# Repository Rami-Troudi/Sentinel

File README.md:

# Sentinel

Plateforme de prévention routière basée sur un boîtier embarqué, de l’analyse IA et un système de récompenses pour la conduite responsable.  
Projet développé dans le cadre du hackathon **Hack For Good 4.0 – Forum INSAT Entreprise**, en partenariat avec **Lloyd Assurance**.

---

## 1. Introduction

**Sentinel** est une solution de télématique intelligente qui combine :

- un **boîtier embarqué ESP32** installé dans le véhicule ;
- une **application mobile** pour le conducteur ;
- une **infrastructure cloud** et une **API backend** ;
- un **module d’intelligence artificielle** pour analyser la conduite ;
- un **dashboard web** pour l’assureur.

L’objectif est double :

1. **Mieux comprendre et anticiper le risque** (conducteurs et zones).  
2. **Encourager et récompenser la conduite responsable** via un système d’éco-points échangeables contre des avantages.

---

## 2. Problématique

Les assureurs automobiles, font face à plusieurs limitations :

- Évaluation du risque principalement **a posteriori**, après sinistre.
- Données comportementales **peu spécifiques** et difficilement exploitables.
- Solutions basées sur smartphone **peu fiables** (capteurs limités, usage intermittent, contournement possible).
- **Absence d’incitation positive** claire pour encourager la bonne conduite.
- Manque de **cartographie dynamique** des zones routières à risque.
- Nécessité de s’inscrire dans une démarche **RSE** crédible (sécurité, éco-conduite, inclusion).

Conséquences :

- sinistralité plus élevée que nécessaire ;
- difficulté à adapter les primes au comportement réel ;
- faible engagement des assurés ;
- opportunités perdues en matière de prévention et de fidélisation.

---

## 3. Description de la solution

### 3.1 Vue d’ensemble

Sentinel propose un écosystème complet qui relie :

- les **données terrain** (capteurs dans le véhicule) ;
- une **analyse IA** à plusieurs niveaux (événements, comportements, zones) ;
- un **système de scoring** et de **classification des risques** ;
- un **programme d’éco-points** qui transforme la prévention en valeur pour le client ;
- un **outil de pilotage** pour l’assureur.

### 3.2 Fonctionnalités principales

- Collecte de télémétrie : accélérations, freinages brusques, virages, vibrations, etc.
- Détection d’événements de conduite à risque.
- Calcul d’un **score de conduite dynamique** pour chaque conducteur.
- Classification des **zones géographiques à risque**.
- Génération d’**éco-points** pour les conducteurs responsables.
- Échange des éco-points contre :
  - réductions sur la prime d’assurance,
  - bons et avantages chez les partenaires de l’assureur.
- Dashboard pour Lloyd :
  - vision agrégée des risques,
  - cartographie des zones,
  - suivi des indicateurs RSE et du programme de récompenses.
  - Classification des conduteurs selon le risque

---

## 4. Schématisation de la communication dans le système

Schéma logique des flux de données et des interactions :

```text

           │
           ▼
   [Boîtier embarqué ESP32]
  - Capteurs (accéléromètre, gyroscope,
  vibration, etc.)
  - Prétraitement local (seuils)
           │
    Wi-Fi / Bluetooth 
           │
           ▼
      [Application Mobile]
  - Ingestion des données
  - Authentification & sécurité
  - Stockage (base de données)
           │
   ┌───────┴───────────────────┐
   ▼                           ▼ 
[Service IA Cloud]     [Base de données]
- Feature eng.        - Historique scores
- Classification      - Scores
- Scoring             - Éco-points
           │
   ┌───────┴───────────────┐
   ▼                       ▼
[Application mobile]   [Dashboard assureur]
- Score conducteur     - Vue portefeuille
- Historique scores   - Segmentation
- Éco-points           - Zones à risque
- Récompenses          - KPIs RSE / sinistres
```

---

## 5. Technologies utilisées

### 5.1 Boîtier embarqué (ESP32 / IoT)

- **Carte** : ESP32.  
- **Langage** : C / C++ (Arduino / ESP-IDF).  
- **Capteurs** :
  - IMU (accéléromètre + gyroscope),
  - capteur de vibrations,
  - capteur GPS
  - capteurs de Tension batterie
- **Rôle** :
  - collecte des données brutes,
  - filtrage et prétraitement (seuils, moyennes),
  - envoi périodique ou en quasi-temps réel vers l'application mobile.

### 5.2 Backend & API

- **Langage** : Node.js (TypeScript ou JavaScript).  
- **Framework** : Express ou Fastify.  
- **Base de données** : PostgreSQL ou MongoDB.  
- **Responsabilités principales** :
  - endpoints d’ingestion de télémétrie,
  - gestion des utilisateurs (conducteurs, assureurs),
  - calcul et mise à jour des scores,
  - gestion des éco-points (crédit, débit, historique),
  - exposition d’API pour l’application mobile et le dashboard.

### 5.3 Intelligence Artificielle

- **Langage** : Python.  
- **Bibliothèques** : NumPy, Pandas, scikit-learn.  
- **Fonctions IA** :
  - classification de segments de conduite (normal, agressif, risqué),
  - détection d’événements critiques (freinage brusque, virage sec, oscillations anormales),
  - scoring global du conducteur,
  - analyse des corrélations entre segments de route et risque (zones à risque).

### 5.4 Application mobile conducteur

- **Technologie**: Flutter ou React Native.  
- **Fonctionnalités** :
  - Collecte des données du boitier
  - affichage du **score de conduite** (global et par trajet),
  - consultation de l’**historique des scores** et événements,
  - affichage et gestion des **éco-points**,
  - catalogue des **récompenses** (réductions, bons, avantages partenaires),
  - notifications de feedback (alertes, conseils d’amélioration).

### 5.5 Dashboard assureur

- **Frontend** : React ou Next.js.  
- **Visualisation** : Recharts, Chart.js ou équivalent.  
- **Fonctionnalités** :
  - vue d’ensemble des conducteurs classés par niveau de risque,
  - filtres par profil, zone, période,
  - cartographie des zones à risque (intégration API de carte),
  - suivi de l’émission et de l’utilisation des éco-points,
  - indicateurs de performance (évolution des scores, baisse des événements critiques, etc.).

### 5.6 Infrastructure & déploiement (prototype)

- Hébergement cloud (type PaaS : Render, Railway, Heroku ou autre).
- CI/CD simple via GitHub Actions (tests de base, déploiement).
- Sécurisation minimale des endpoints (HTTPS, tokens, etc., selon l’avancement).

---

## 6. Marketing et positionnement

**Pour les conducteurs :**

- accès à un score de conduite clair et pédagogique ;
- possibilité de **gagner des éco-points** en améliorant leur comportement ;
- conversion des points en **avantages concrets** (réductions, bons, services).

**Pour l’assureur (Lloyd) :**

- meilleure **segmentation des clients** par niveau de risque réel ;
- réduction de la sinistralité grâce à la prévention ;
- offre différenciante, orientée **RSE** et innovation ;
- programme de fidélisation basé sur des récompenses plutôt que sur la sanction.

**Pour les partenaires :**

- visibilité auprès de conducteurs engagés ;
- intégration de leurs offres dans un écosystème à forte valeur ajoutée.

---

## 8. Contexte Hack For Good 4.0

Le projet est développé dans le cadre du hackathon **Hack For Good 4.0** dont les axes incluent :

- **prévention routière**,  
- **mobilité responsable**,  
- intégration de l’**IA** dans une démarche RSE.

Sentinel vise à :

- adresser une problématique réelle et prioritaire pour l’assurance ;
- démontrer une **intégration IA crédible** et cohérente ;
- proposer un prototype techniquement réalisable dans les contraintes du hackathon ;
- mettre en avant un **impact RSE** mesurable (sécurité, éco-conduite, inclusion).

---

## 9. Avertissement

Ce dépôt correspond à un **prototype de hackathon** :

- le code est en cours d’évolution ;
- certains modules sont partiellement implémentés ou simulés ;
- la solution n’est pas destinée à un usage en production sans durcissement, revue de sécurité et validation approfondie.

---

## 10. Crédits

Projet **Sentinel** — développé par l’équipe cham3a^2 au **Hack For Good 4.0 – Forum INSAT Entreprise**, en collaboration avec **Lloyd Assurance**.

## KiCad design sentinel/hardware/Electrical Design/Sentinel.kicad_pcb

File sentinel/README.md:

# Sentinel
Prototype structure placeholder.

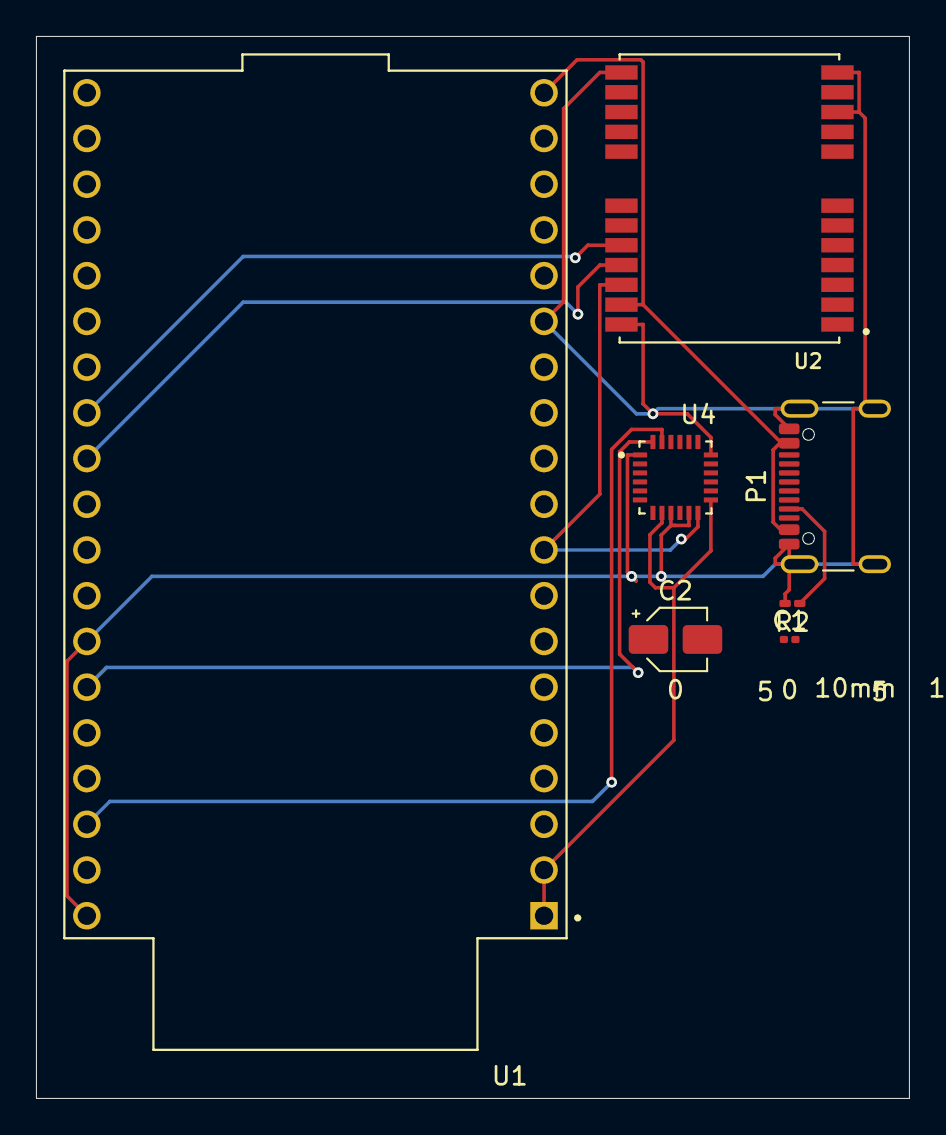
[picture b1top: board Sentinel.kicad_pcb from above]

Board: 2 copper layers, 48.5 x 59.0 mm, 7 parts (0 on the bottom side), 9 nets.

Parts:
C1: 0.1u; C_0201_0603Metric
C2: 2.2n; CP_Elec_3x5.4
P1: USB_C_Plug_USB2.0; USB_C_Receptacle_GCT_USB4105-xx-A_16P_TopMnt_Horizontal
R2: 5.1k; R_0201_0603Metric_Pad0.64x0.40mm_HandSolder
U1: ESP32-DEVKITC; MODULE_ESP32-DEVKITC
U2: NEO-6M-GPS; XCVR_NEO-6M-GPS
U4: MPU-6050-A; QFN50P400X400X95-24N

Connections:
GND: P1.A1 (GND), P1.A12 (GND), P1.B1 (GND), P1.B12 (GND), P1.S1 (SHIELD), R2.2, U1.14 (GND1), U1.32 (GND2), U1.38 (GND3), U2.10 (GND), U2.12 (GND), U2.13 (GND), U2.24 (GND), U4.1 (CLKIN), U4.9 (AD0), U4.11 (FSYNC), U4.18 (GND)
unnamed: P1.A5 (CC), R2.1
unnamed: U1.1 (3V3), U1.2 (EN), U4.8 (VLOGIC), U4.13 (VDD)
unnamed: P1.A4 (VBUS), P1.A9 (VBUS), P1.B4 (VBUS), P1.B9 (VBUS), U1.19 (EXT_5V), U2.23 (VCC)
unnamed: U1.27 (IO16), U2.20 (TXD1)
unnamed: U1.28 (IO17), U2.21 (RXD1)
unnamed: U1.33 (IO21), U4.24 (SDA)
unnamed: U1.36 (IO22), U4.23 (SCL)
unnamed: U1.9 (IO25), U2.22 (V_BCKP), U4.12 (INT)

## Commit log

2025-11-16 Structure Initialisation
    Setting up the main structure of the project prior to starting the work on it
2025-11-16 Readme Writing
2025-11-16 Update AI functions list in README
    Removed a bullet point about feature extraction from the AI functions section.
2025-11-16 Create Hardware
2025-11-16 Create placeholder
2025-11-16 Create ESP32 Code
2025-11-16 Rename ESP32 Code to ESP32 Code.cpp
2025-11-16 Create Design
2025-11-16 Expand README with AI module details
    Added detailed information about the AI module for driving analysis, including its purpose, contents, and role in scoring.
2025-11-16 Expand README.md with mobile app details
    Added detailed documentation for the mobile app, including features, structure, demo mode operation, and launch instructions.
2025-11-16 Delete app launch instructions from README
    Removed instructions for launching the app with React Native and Expo.
2025-11-16 Expand README with dashboard details and usage
    Added detailed information about the dashboard application, its structure, usage scenario, and setup instructions.
2025-11-16 Update README for dashboard application
2025-11-16 Enhance README with firmware module details
    Added detailed information about the firmware module, its structure, and demo mode capabilities.
2025-11-16 Uploaded Circuit design files
2025-11-17 First mobile prototype, not yet functional
2025-11-17 Add mobile Flutter project prototype
2025-11-17 Create temp
2025-11-17 First prototype
2025-11-17 Business Understanding
2025-11-18 Current working mobile app prototype
    A first foundation in the mobile app for testing purposes. Includes some functionalities. Connectivity is not yet assured but is the next step in the app development alongside with the UI
2025-11-18 Créé à l'aide de Colab
2025-11-18 Sentinel wireframe
    Imported the 1st draft of Sentinels' wireframe
2025-11-18 ESP32 FIRST PROTOTYPE
